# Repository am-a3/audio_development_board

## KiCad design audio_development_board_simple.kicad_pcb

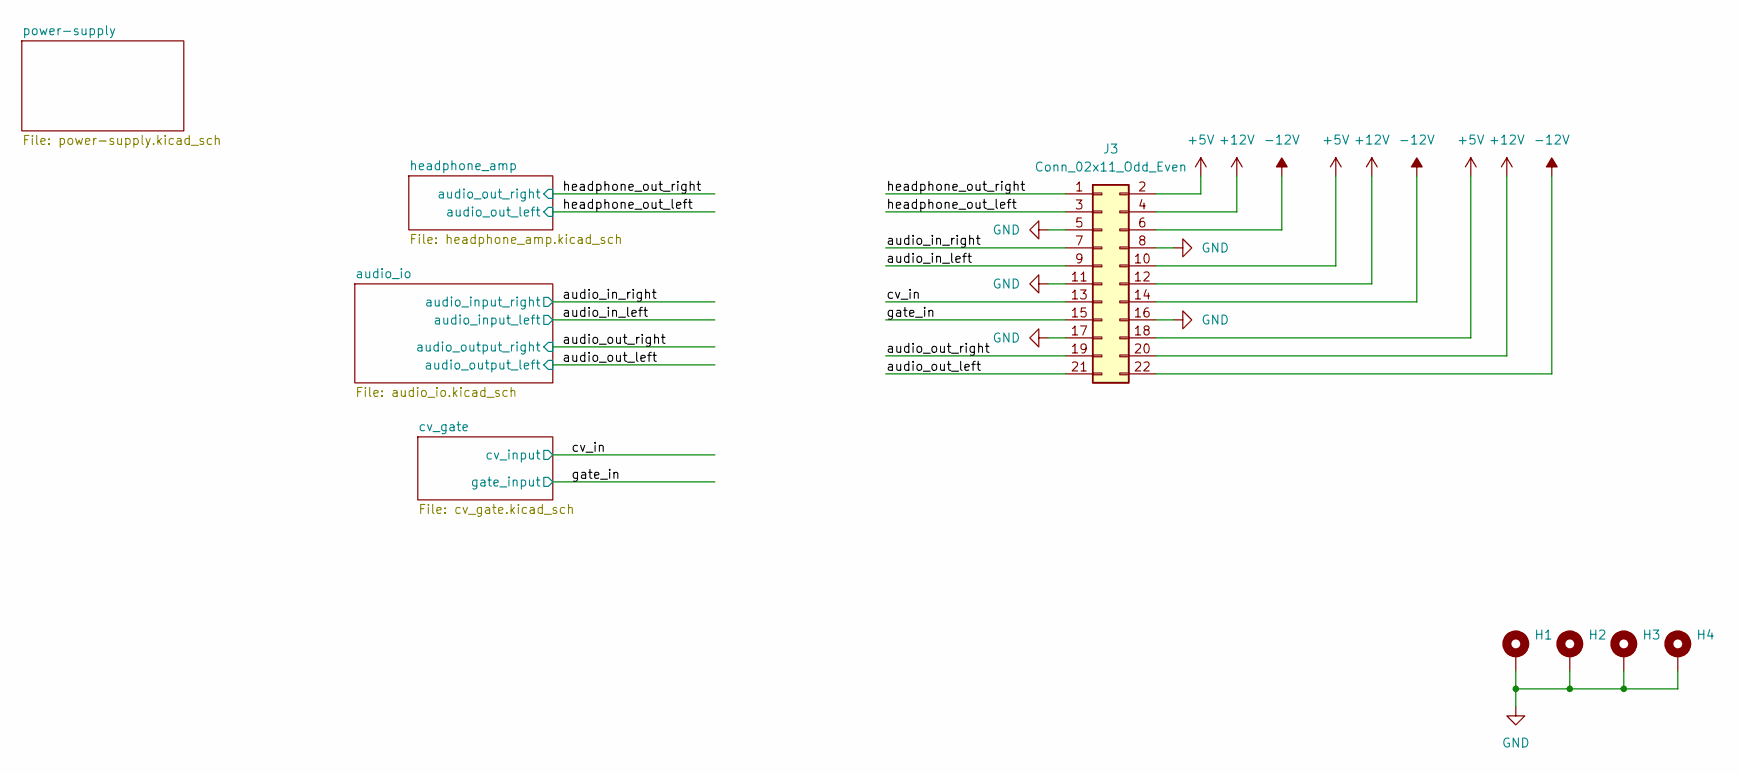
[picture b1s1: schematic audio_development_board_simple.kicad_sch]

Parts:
H1, H2, H3, H4: MountingHole_Pad; MountingHole_3.2mm_M3_ISO7380_Pad
J3: Conn_02x11_Odd_Even; PinSocket_2x11_P2.54mm_Vertical

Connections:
+5V: J3.2, J3.10, J3.18; also elsewhere on the board
+12V: J3.4, J3.12, J3.20; also elsewhere on the board
-12V: J3.6, J3.14, J3.22; also elsewhere on the board
/audio_in_left: J3.9; also elsewhere on the board
/audio_in_right: J3.7; also elsewhere on the board
/audio_out_left: J3.21; also elsewhere on the board
/audio_out_right: J3.19; also elsewhere on the board
/cv_in: J3.13; also elsewhere on the board
/gate_in: J3.15; also elsewhere on the board
/headphone_out_left: J3.3; also elsewhere on the board
/headphone_out_right: J3.1; also elsewhere on the board
GND: H1.1, H2.1, H3.1, H4.1, J3.5, J3.8, J3.11, J3.16, J3.17; also elsewhere on the board

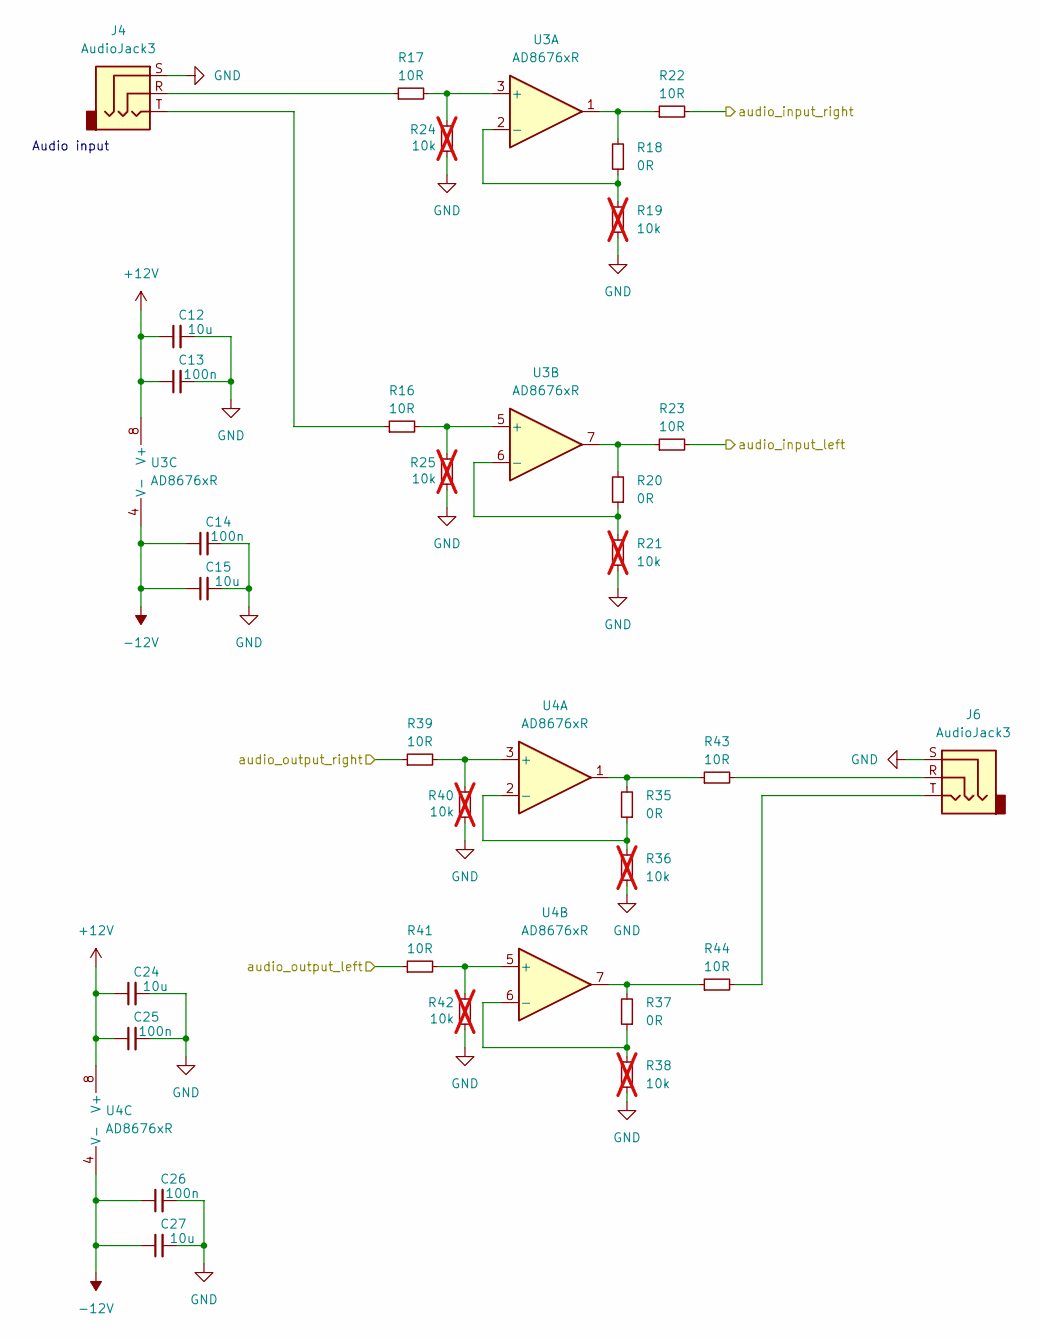
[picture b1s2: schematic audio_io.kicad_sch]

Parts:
C12, C15, C24, C27: 10u; C_1206_3216Metric
C13, C14, C25, C26: 100n; C_0603_1608Metric_Pad1.08x0.95mm_HandSolder
J4, J6: AudioJack3; Jack_3.5mm_Lumberg_1503_02_Horizontal
R16, R17, R22, R23, R39, R41, R43, R44: 10R; R_0603_1608Metric_Pad0.98x0.95mm_HandSolder
R18, R20, R35, R37: 0R; R_0603_1608Metric_Pad0.98x0.95mm_HandSolder
R19, R21, R24, R25, R36, R38, R40, R42: 10k; R_0603_1608Metric_Pad0.98x0.95mm_HandSolder; not fitted
U3, U4: AD8676xR; SOIC-8_3.9x4.9mm_P1.27mm

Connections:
+12V: C12.1, C13.1, C24.1, C25.1, U3.8 (V+), U4.8 (V+); also elsewhere on the board
-12V: C14.1, C15.1, C26.1, C27.1, U3.4 (V-), U4.4 (V-); also elsewhere on the board
/audio_in_left: R23.2; also elsewhere on the board
/audio_in_right: R22.2; also elsewhere on the board
/audio_out_left: R41.1; also elsewhere on the board
/audio_out_right: R39.1; also elsewhere on the board
GND: C12.2, C13.2, C14.2, C15.2, C24.2, C25.2, C26.2, C27.2, J4.S, J6.S, R19.1, R21.1, R24.1, R25.1, R36.1, R38.1, R40.1, R42.1; also elsewhere on the board
unnamed: J4.R, R17.1
unnamed: J4.T, R16.1
unnamed: J6.R, R43.2
unnamed: J6.T, R44.2
unnamed: R18.2, R22.1, U3.1
unnamed: R20.2, R23.1, U3.7
unnamed: R35.2, R43.1, U4.1
unnamed: R37.2, R44.1, U4.7
unnamed: R17.2, R24.2, U3.3 (+)
unnamed: R18.1, R19.2, U3.2 (-)
unnamed: R16.2, R25.2, U3.5 (+)
unnamed: R20.1, R21.2, U3.6 (-)
unnamed: R39.2, R40.2, U4.3 (+)
unnamed: R35.1, R36.2, U4.2 (-)
unnamed: R41.2, R42.2, U4.5 (+)
unnamed: R37.1, R38.2, U4.6 (-)

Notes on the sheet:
Audio input

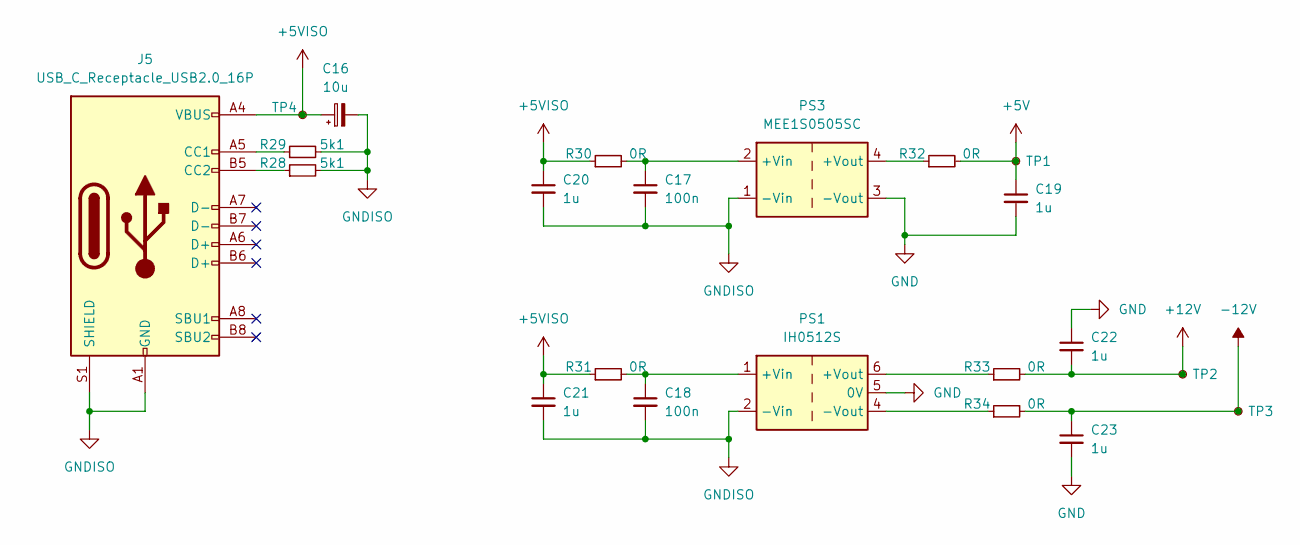
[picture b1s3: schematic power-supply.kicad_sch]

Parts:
C16: 10u; CP_EIA-3216-18_Kemet-A
C17, C18: 100n; C_0603_1608Metric_Pad1.08x0.95mm_HandSolder
C19, C20, C21, C22, C23: 1u; C_0603_1608Metric_Pad1.08x0.95mm_HandSolder
J5: USB_C_Receptacle_USB2.0_16P; USB_C_Receptacle_GCT_USB4110
PS1: IH0512S; Converter_DCDC_XP_POWER-IHxxxxS_THT
PS3: MEE1S0505SC; Converter_DCDC_Murata_MEE1SxxxxSC_THT
R28, R29: 5k1; R_0603_1608Metric_Pad0.98x0.95mm_HandSolder
R30, R31, R32, R33, R34: 0R; R_0603_1608Metric_Pad0.98x0.95mm_HandSolder
TP1, TP2, TP3, TP4: TestPoint_Small; TestPoint_Pad_D1.5mm

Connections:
+5V: C19.1, R32.2, TP1.1; also elsewhere on the board
+5VISO: C16.1, C20.1, C21.1, J5.A4 (VBUS), J5.A9 (VBUS), J5.B4 (VBUS), J5.B9 (VBUS), R30.1, R31.1, TP4.1
+12V: C22.2, R33.2, TP2.1; also elsewhere on the board
-12V: C23.1, R34.2, TP3.1; also elsewhere on the board
GND: C19.2, C22.1, C23.2, PS1.5 (0V), PS3.3 (-Vout); also elsewhere on the board
GNDISO: C16.2, C17.2, C18.2, C20.2, C21.2, J5.A1 (GND), J5.A12 (GND), J5.B1 (GND), J5.B12 (GND), J5.S1 (SHIELD), PS1.2 (-Vin), PS3.1 (-Vin), R28.2, R29.2
unnamed: J5.A5 (CC1), R29.1
unnamed: J5.B5 (CC2), R28.1
unnamed: C18.1, PS1.1 (+Vin), R31.2
unnamed: PS1.6 (+Vout), R33.1
unnamed: PS1.4 (-Vout), R34.1
unnamed: C17.1, PS3.2 (+Vin), R30.2
unnamed: PS3.4 (+Vout), R32.1

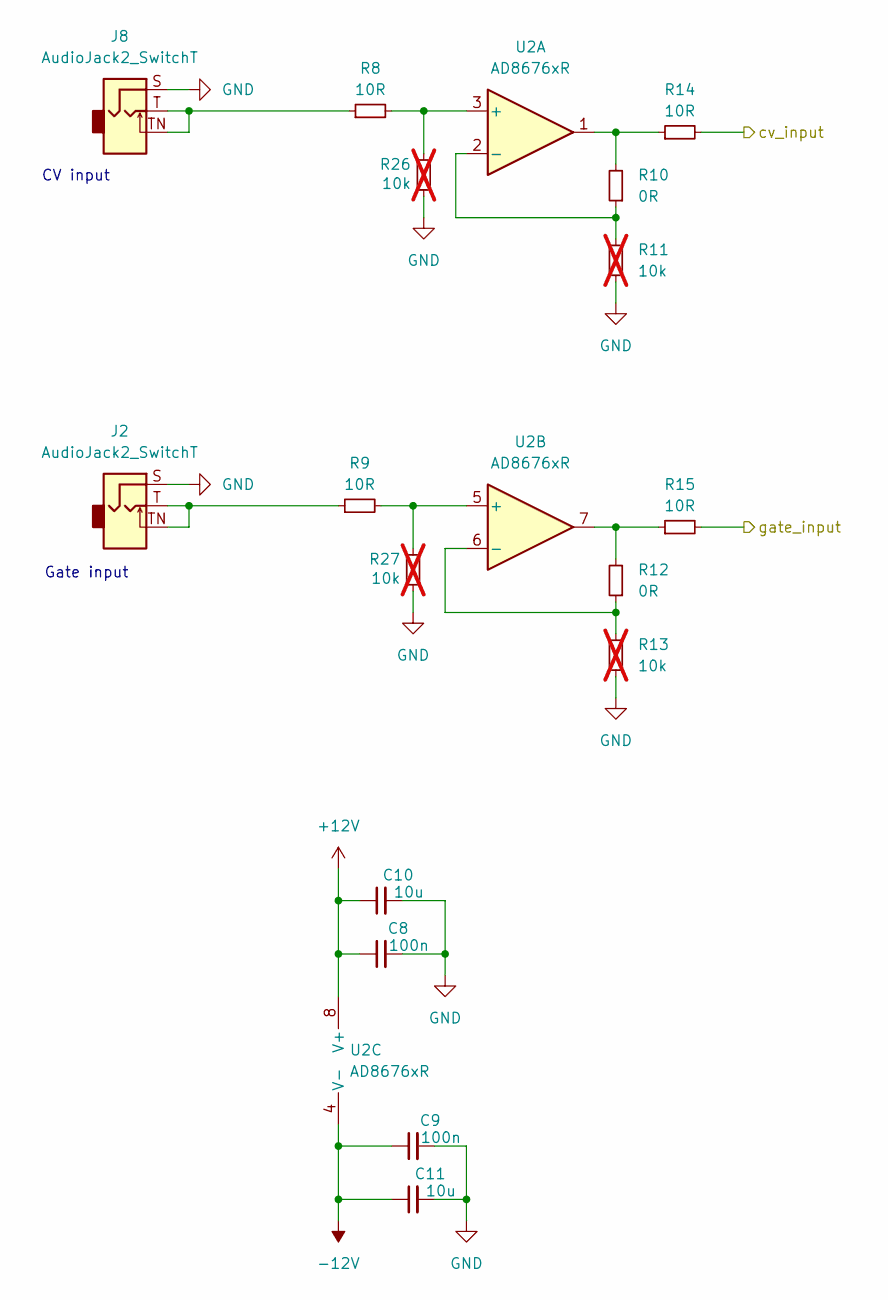
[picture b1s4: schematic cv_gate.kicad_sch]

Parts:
C8, C9: 100n; C_0603_1608Metric_Pad1.08x0.95mm_HandSolder
C10, C11: 10u; C_1206_3216Metric
J2, J8: AudioJack2_SwitchT; MJ-3523-SMT-TR
R8, R9, R14, R15: 10R; R_0603_1608Metric_Pad0.98x0.95mm_HandSolder
R10, R12: 0R; R_0603_1608Metric_Pad0.98x0.95mm_HandSolder
R11, R13, R26, R27: 10k; R_0603_1608Metric_Pad0.98x0.95mm_HandSolder; not fitted
U2: AD8676xR; SOIC-8_3.9x4.9mm_P1.27mm

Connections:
+12V: C8.1, C10.1, U2.8 (V+); also elsewhere on the board
-12V: C9.1, C11.1, U2.4 (V-); also elsewhere on the board
/cv_in: R14.2; also elsewhere on the board
/gate_in: R15.2; also elsewhere on the board
GND: C8.2, C9.2, C10.2, C11.2, J2.S, J8.S, R11.1, R13.1, R26.1, R27.1; also elsewhere on the board
unnamed: J2.T, J2.TN, R9.1
unnamed: J8.T, J8.TN, R8.1
unnamed: R10.2, R14.1, U2.1
unnamed: R12.2, R15.1, U2.7
unnamed: R8.2, R26.2, U2.3 (+)
unnamed: R10.1, R11.2, U2.2 (-)
unnamed: R9.2, R27.2, U2.5 (+)
unnamed: R12.1, R13.2, U2.6 (-)

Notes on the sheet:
CV input
Gate input

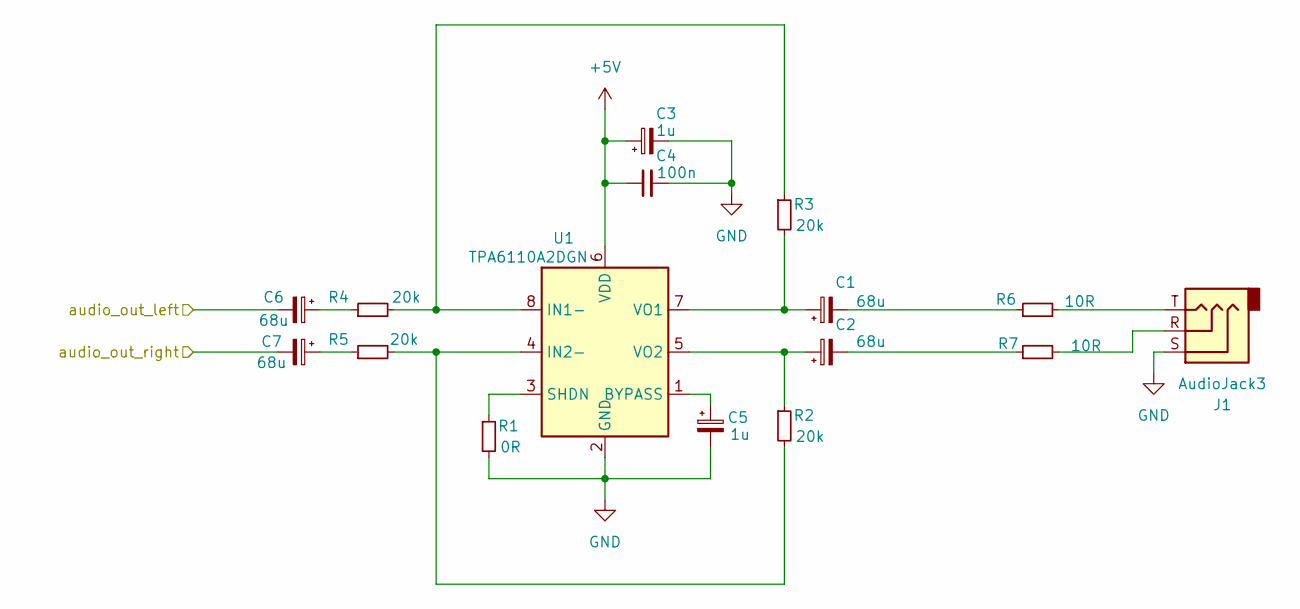
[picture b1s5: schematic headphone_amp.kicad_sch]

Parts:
C1, C2, C6, C7: 68u; CP_EIA-7343-31_Kemet-D_Pad2.25x2.55mm_HandSolder; Part Number 293D686X9020D2TE3
C3, C5: 1u; CP_EIA-3216-18_Kemet-A
C4: 100n; C_0603_1608Metric_Pad1.08x0.95mm_HandSolder
J1: AudioJack3; Jack_3.5mm_Lumberg_1503_02_Horizontal
R1: 0R; R_0603_1608Metric_Pad0.98x0.95mm_HandSolder
R2, R3, R4, R5: 20k; R_0603_1608Metric_Pad0.98x0.95mm_HandSolder
R6, R7: 10R; R_0603_1608Metric_Pad0.98x0.95mm_HandSolder
U1: TPA6110A2DGN; HVSSOP-8-1EP_3x3mm_P0.65mm_EP1.57x1.89mm

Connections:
+5V: C3.1, C4.1, U1.6 (VDD); also elsewhere on the board
/headphone_out_left: C6.2; also elsewhere on the board
/headphone_out_right: C7.2; also elsewhere on the board
GND: C3.2, C4.2, C5.2, J1.S, R1.2, U1.2 (GND), U1.9 (GND); also elsewhere on the board
unnamed: C1.2, R6.1
unnamed: C2.2, R7.1
unnamed: C6.1, R4.1
unnamed: C7.1, R5.1
unnamed: J1.R, R7.2
unnamed: J1.T, R6.2
unnamed: C5.1, U1.1 (BYPASS)
unnamed: R3.1, R4.2, U1.8 (IN1-)
unnamed: R2.2, R5.2, U1.4 (IN2-)
unnamed: R1.1, U1.3 (SHDN)
unnamed: C1.1, R3.2, U1.7 (VO1)
unnamed: C2.1, R2.1, U1.5 (VO2)

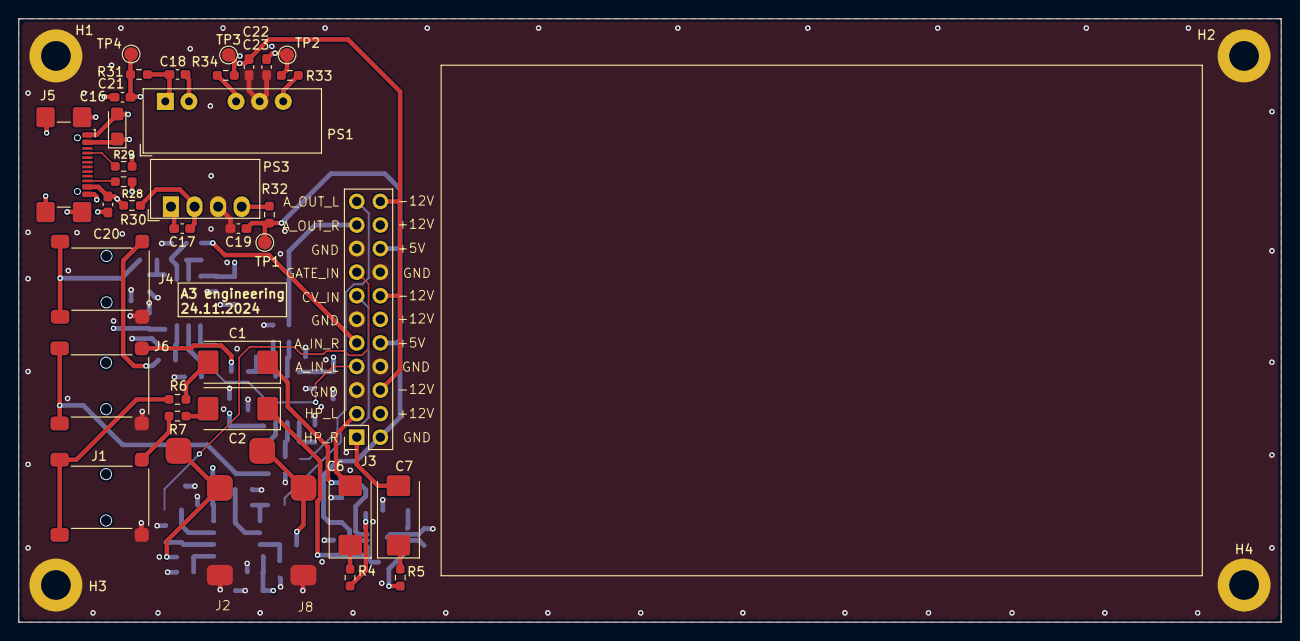
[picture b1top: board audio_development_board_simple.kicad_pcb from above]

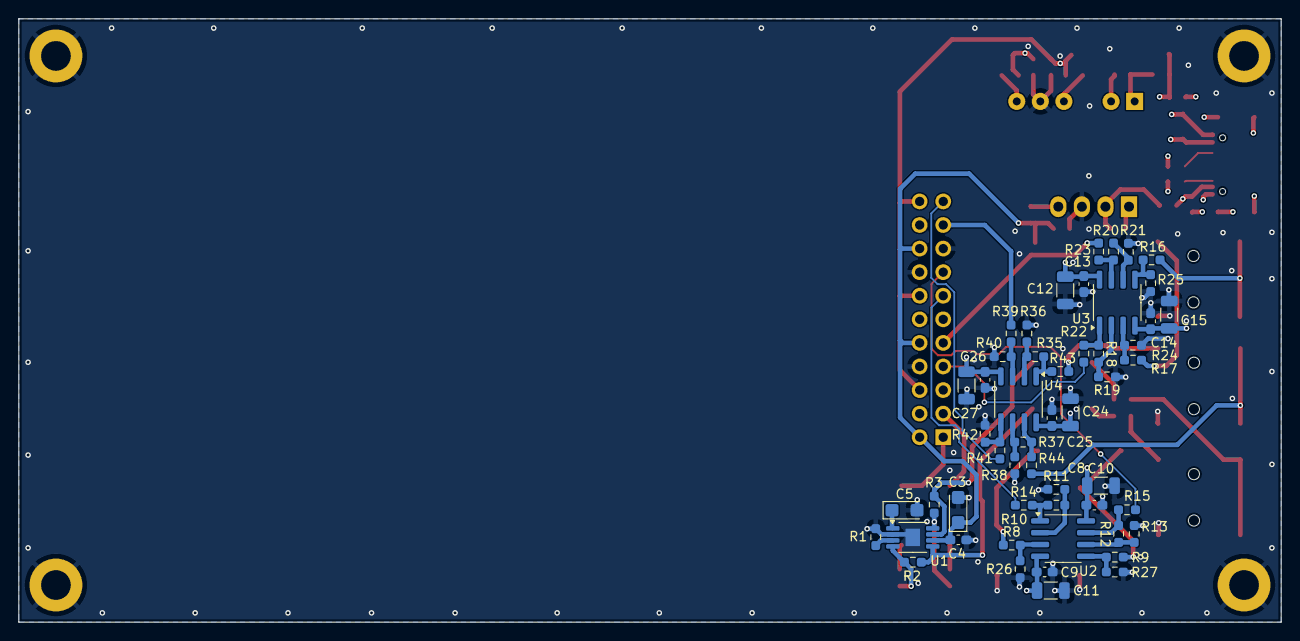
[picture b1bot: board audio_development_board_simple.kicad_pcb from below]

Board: 4 copper layers, 136.0 x 65.0 mm, 92 parts (52 on the bottom side), 57 nets.

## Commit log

2024-11-25 Initial release for manufacturing v01
